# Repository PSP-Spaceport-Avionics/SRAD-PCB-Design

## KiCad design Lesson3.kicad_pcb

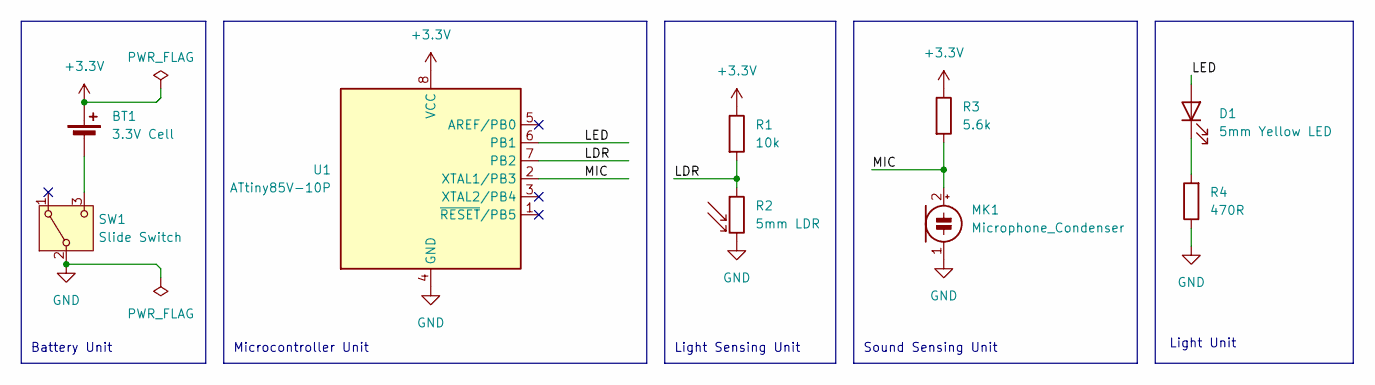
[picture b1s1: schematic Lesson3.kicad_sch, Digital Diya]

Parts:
BT1: 3.3V Cell; BatteryHolder_ComfortableElectronic_CH273-2450_1x2450
D1: 5mm Yellow LED; LED_D5.0mm
MK1: Microphone_Condenser; PinHeader_1x02_P2.54mm_Vertical
R1: 10k; R_Axial_DIN0207_L6.3mm_D2.5mm_P15.24mm_Horizontal
R2: 5mm LDR; R_LDR_5.1x4.3mm_P3.4mm_Vertical
R3: 5.6k; R_Axial_DIN0207_L6.3mm_D2.5mm_P15.24mm_Horizontal
R4: 470R; R_Axial_DIN0207_L6.3mm_D2.5mm_P15.24mm_Horizontal
SW1: Slide Switch; SW_E-Switch_EG1224_SPDT_Angled
U1: ATtiny85V-10P; DIP-8_W7.62mm

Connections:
+3.3V: BT1.1 (+), R1.1, R3.1, U1.8 (VCC)
/LDR: R1.2, R2.1, U1.7 (PB2)
/LED: D1.2 (A), U1.6 (PB1)
/MIC: MK1.2 (+), R3.2, U1.2 (XTAL1/PB3)
GND: MK1.1 (-), R2.2, R4.1, SW1.2 (B), U1.4 (GND)
unnamed: BT1.2 (-), SW1.3 (C)
unnamed: D1.1 (K), R4.2

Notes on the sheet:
Sound Sensing Unit
Battery Unit
Microcontroller Unit
Light Unit
Light Sensing Unit

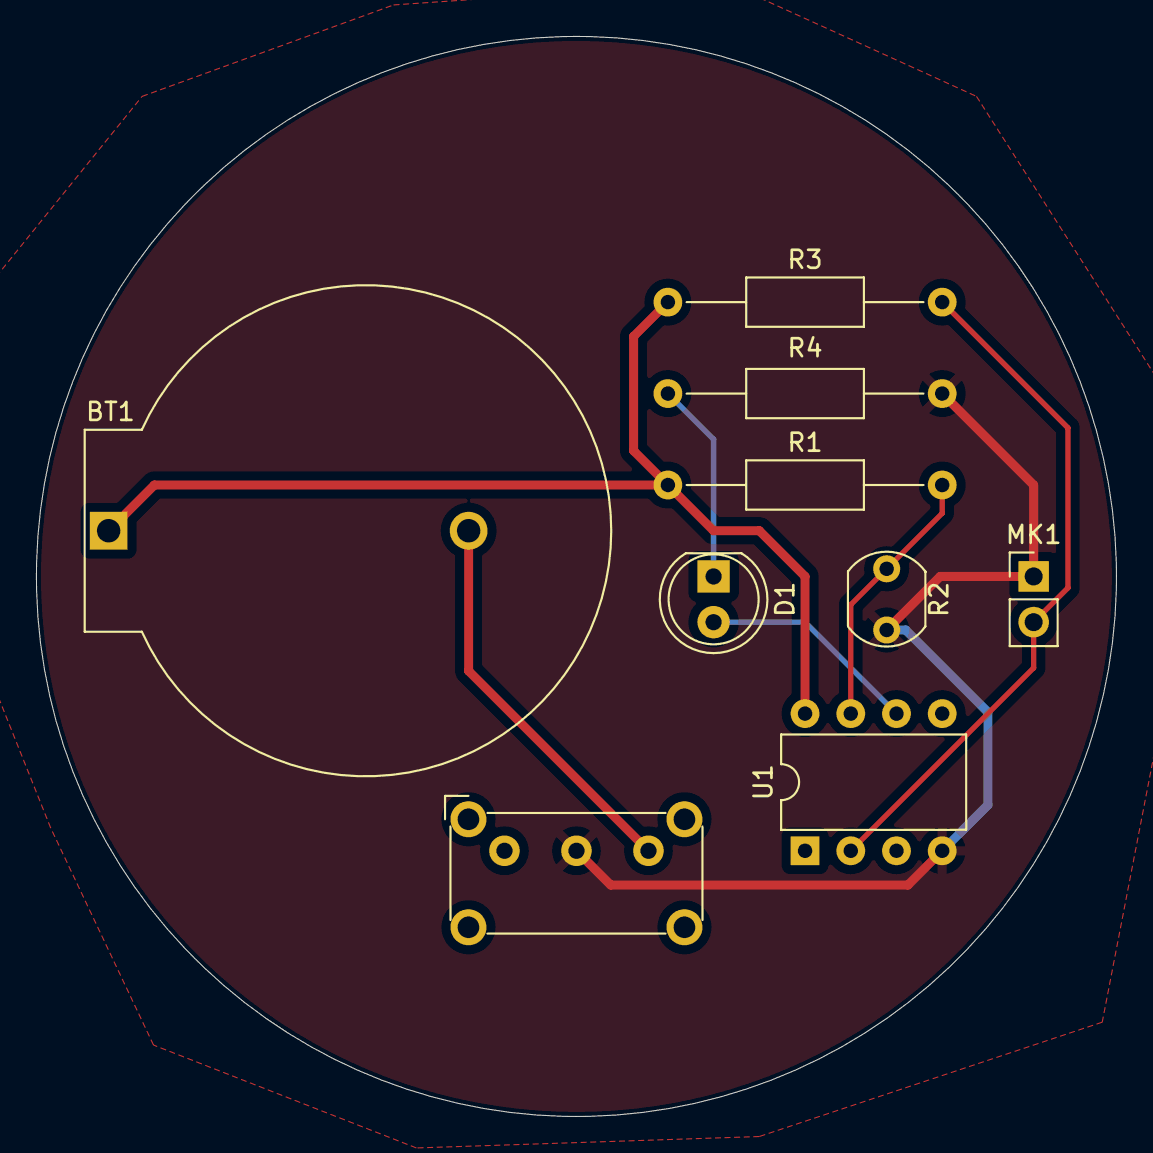
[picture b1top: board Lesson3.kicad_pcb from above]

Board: 2 copper layers, 60.0 x 60.0 mm, 9 parts (0 on the bottom side), 7 nets.
